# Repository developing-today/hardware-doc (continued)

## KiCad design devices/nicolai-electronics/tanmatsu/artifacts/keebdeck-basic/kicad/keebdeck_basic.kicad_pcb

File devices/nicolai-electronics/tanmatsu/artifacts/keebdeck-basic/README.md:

# KeebDeck Basic — reference-board schematic and KiCad source

Solder Party's **KeebDeck Basic** evaluation board — the reference design for driving a KeebDeck
keypad. The Tanmatsu does **not** ship this board; it is prior art for the Tanmatsu's own keyboard
section.

| | |
|---|---|
| `keebdeck-basic-schematic-rev1.1.pdf` | the exported schematic — filed 2026-09-20, mined in [`../../keyboard.md` §2b](../../keyboard.md) |
| `kicad/` | **the EDA source it was exported from** — added 2026-09-20, see §"KiCad source" |
| `mechanical/` | STEP models — **archived** 2026-09-20, placeholders in place |
| `LICENSE-CERN-OHL-v1.2.md` | upstream `LICENSE.md` — **read 2026-09-20**, see the correction below |
| `upstream-README.md` | upstream `README.md` |

## The PDF

`keebdeck-basic-schematic-rev1.1.pdf`

| Field | Value |
|---|---|
| What it is | Schematic of the **Solder Party KeebDeck Basic** evaluation board — the reference design for driving a KeebDeck keypad |
| Upstream repository | <https://github.com/solderparty/keebdeck_basic_hw> |
| Commit | **`2b537ce`** — commit subject *"Rev 1.1 - Production"* |
| Member path in repo | `schematics.pdf` |
| Source file | `keebdeck_basic.kicad_sch`, exported by KiCad E.D.A. **9.0.1** (Eeschema-PDF) |
| PDF `CreationDate` | **2025-05-04** |
| Title-block `Date:` / `Rev:` | **blank** — the "Rev 1.1" label comes from the Git commit only |
| Bytes | **355 080** |
| SHA-256 | `593aa32d45e70aaa331f82b558a5675666e5bd2d0f7f9584e36abfbb66b8b0a4` |
| Pages | 1 (A4 landscape, 841.896 × 595.296 pt) |
| Retrieved | **2026-08-24** (with the rest of the Tanmatsu source clones) |
| Filed here | **2026-09-20** |
| Renamed | from `schematics.pdf` → `keebdeck-basic-schematic-rev1.1.pdf` |
| Licence | **CERN Open Hardware Licence v1.2** — ✅ **resolved 2026-09-20**, see the correction below |
| Redistribution status | `conditional` — CERN-OHL v1.2 requires notice and licence retention |
| Disposition | `repository` |

> ### ✅ Correction — the licence is now known
>
> This record previously said: *"**unknown** — the upstream repo ships a `LICENSE.md` that was
> **not read** in this pass. The sibling `keebdeck_keyboard_hw` is CERN-OHL v1.2; do **not** assume
> the same applies here."* That caution was correct procedure and is now discharged.
>
> `LICENSE.md` (9 121 B) **was read on 2026-09-20** and is the **CERN Open Hardware Licence
> v1.2** — the same licence as `keebdeck_keyboard_hw` after all. It is retained here as
> `LICENSE-CERN-OHL-v1.2.md`.
>
> ⚠ The file contains **mojibake**: typographic quotes appear as `?` replacement characters
> (`?Licence? means this CERN OHL`). That is how upstream ships it — the bytes were **not**
> altered. It does not affect the licence's identity, which is stated in plain ASCII on line 1.

## Why this is a copy, not a move

`scratch/tanmatsu/sources/keebdeck_basic_hw/` is a **complete, unmodified `git` checkout** at
`2b537ce` (`git status` clean, 2026-09-20). Moving one file out of it would break a reproducible
upstream snapshot for no benefit, so the file was **copied** and the checkout left intact. The
same treatment was given to `keebdeck_keyboard_hw/dimensions.pdf` in the 2026-08-24 pass.

## What was mined out of it

See [`../../keyboard.md` §2b](../../keyboard.md#2b-verified-the-keebdeck-basic-reference-board-read-from-its-schematic).
The headline findings:

- The reference board is a **6 × 12 / 71-key** matrix, **not** the 6 × 13 the finished KeebDeck
  keypad and the Tanmatsu use.
- **No diodes in the matrix.** Ghosting is mitigated by swapping the TAB and E columns, per a
  note on the sheet.
- The **whole backlight block and the boot button are marked DNP**.
- **`ROW3` is `BOOT0`**, and **`COL0`/`COL1` are `SWDIO`/`SWCLK`** — three pins that are both
  matrix lines and system-critical.

## Re-acquisition

```bash
git clone https://github.com/solderparty/keebdeck_basic_hw
git -C keebdeck_basic_hw checkout 2b537ce
sha256sum keebdeck_basic_hw/schematics.pdf
# expect 593aa32d45e70aaa331f82b558a5675666e5bd2d0f7f9584e36abfbb66b8b0a4
```

Reacquisition status: **automatic**. Verified present at that commit on **2026-09-20** from the
local checkout; the GitHub URL was **not** re-probed in this pass.

---

## KiCad source · *added 2026-09-20*

The PDF above is an export. These are the files it was exported from — primary, load-bearing EDA
source, so they belong in the repository rather than the archive.

| File | Bytes | SHA-256 (first 16) |
|---|---:|---|
| `kicad/keebdeck_basic.kicad_sch` | 519 853 | `cc0ce3ffbe3693c6…` |
| `kicad/keebdeck_basic.kicad_pcb` | 2 928 754 | `39b66d2d24ff7a37…` |
| `kicad/keebdeck_basic.kicad_pro` | 16 331 | `4782c9f31bb75540…` |
| `kicad/keebdeck_basic_faceplate.kicad_pcb` | 379 374 | `141f51ef272c238b…` |
| `kicad/keebdeck_basic_faceplate.kicad_pro` | 14 179 | `14ce7942a8c5a528…` |
| `kicad/fp-lib-table`, `kicad/sym-lib-table` | 647 / 611 | library tables |

`keebdeck_basic.kicad_pcb` carries **resolved net names on every pad**, so it — not the PDF, and
not the `.kicad_sch` — is the authoritative statement of this board's connectivity. Re-parse with:

```bash
python3 tools/kicad_pcb_nets.py \
  devices/nicolai-electronics/tanmatsu/artifacts/keebdeck-basic/kicad/keebdeck_basic.kicad_pcb --all
```

### Not copied here

| Left in `scratch/tanmatsu/sources/keebdeck_basic_hw/` | Why |
|---|---|
| `fp-info-cache` (3 950 153 B) | KiCad footprint-index cache — regenerated on open |
| `library/`, `modules/`, `keebdeck_keyboard_hw/` | Git submodule/vendored library trees; the keypad library is already filed at [`../keebdeck-keyboard/`](../keebdeck-keyboard/README.md) |
| `img/basic.jpg` | Product photo, not needed for the electrical record |

## Mechanical models · **archived** 2026-09-20

| File | State | Bytes |
|---|---|---:|
| ~~`mechanical/keebdeck_basic.step`~~ | **archived** → `mechanical/keebdeck_basic.step.ARCHIVED.md` | 46 777 091 |
| ~~`mechanical/keebdeck_basic_faceplate.step`~~ | **archived** → `mechanical/keebdeck_basic_faceplate.step.ARCHIVED.md` | 2 846 452 |

Geometry only, for a board the Tanmatsu does not ship — the clearest possible archive case. Both
placeholders carry SHA-256, byte size, commit `2b537ce`, tag `rev1.1`, author, licence and two
independent recovery URLs, and stand alone without the archive.

## Why these are copies, not moves

Unchanged from the reasoning above: `scratch/tanmatsu/sources/keebdeck_basic_hw/` is a **clean,
unmodified checkout** at `2b537ce` (`git status` clean, 2026-09-20). Every file here was verified
**byte-identical by SHA-256** to its scratch counterpart at copy time; the STEP files were then
archived out of the repository by `tools/archive_artifact.py`, which re-verified content by
fingerprint after the move.

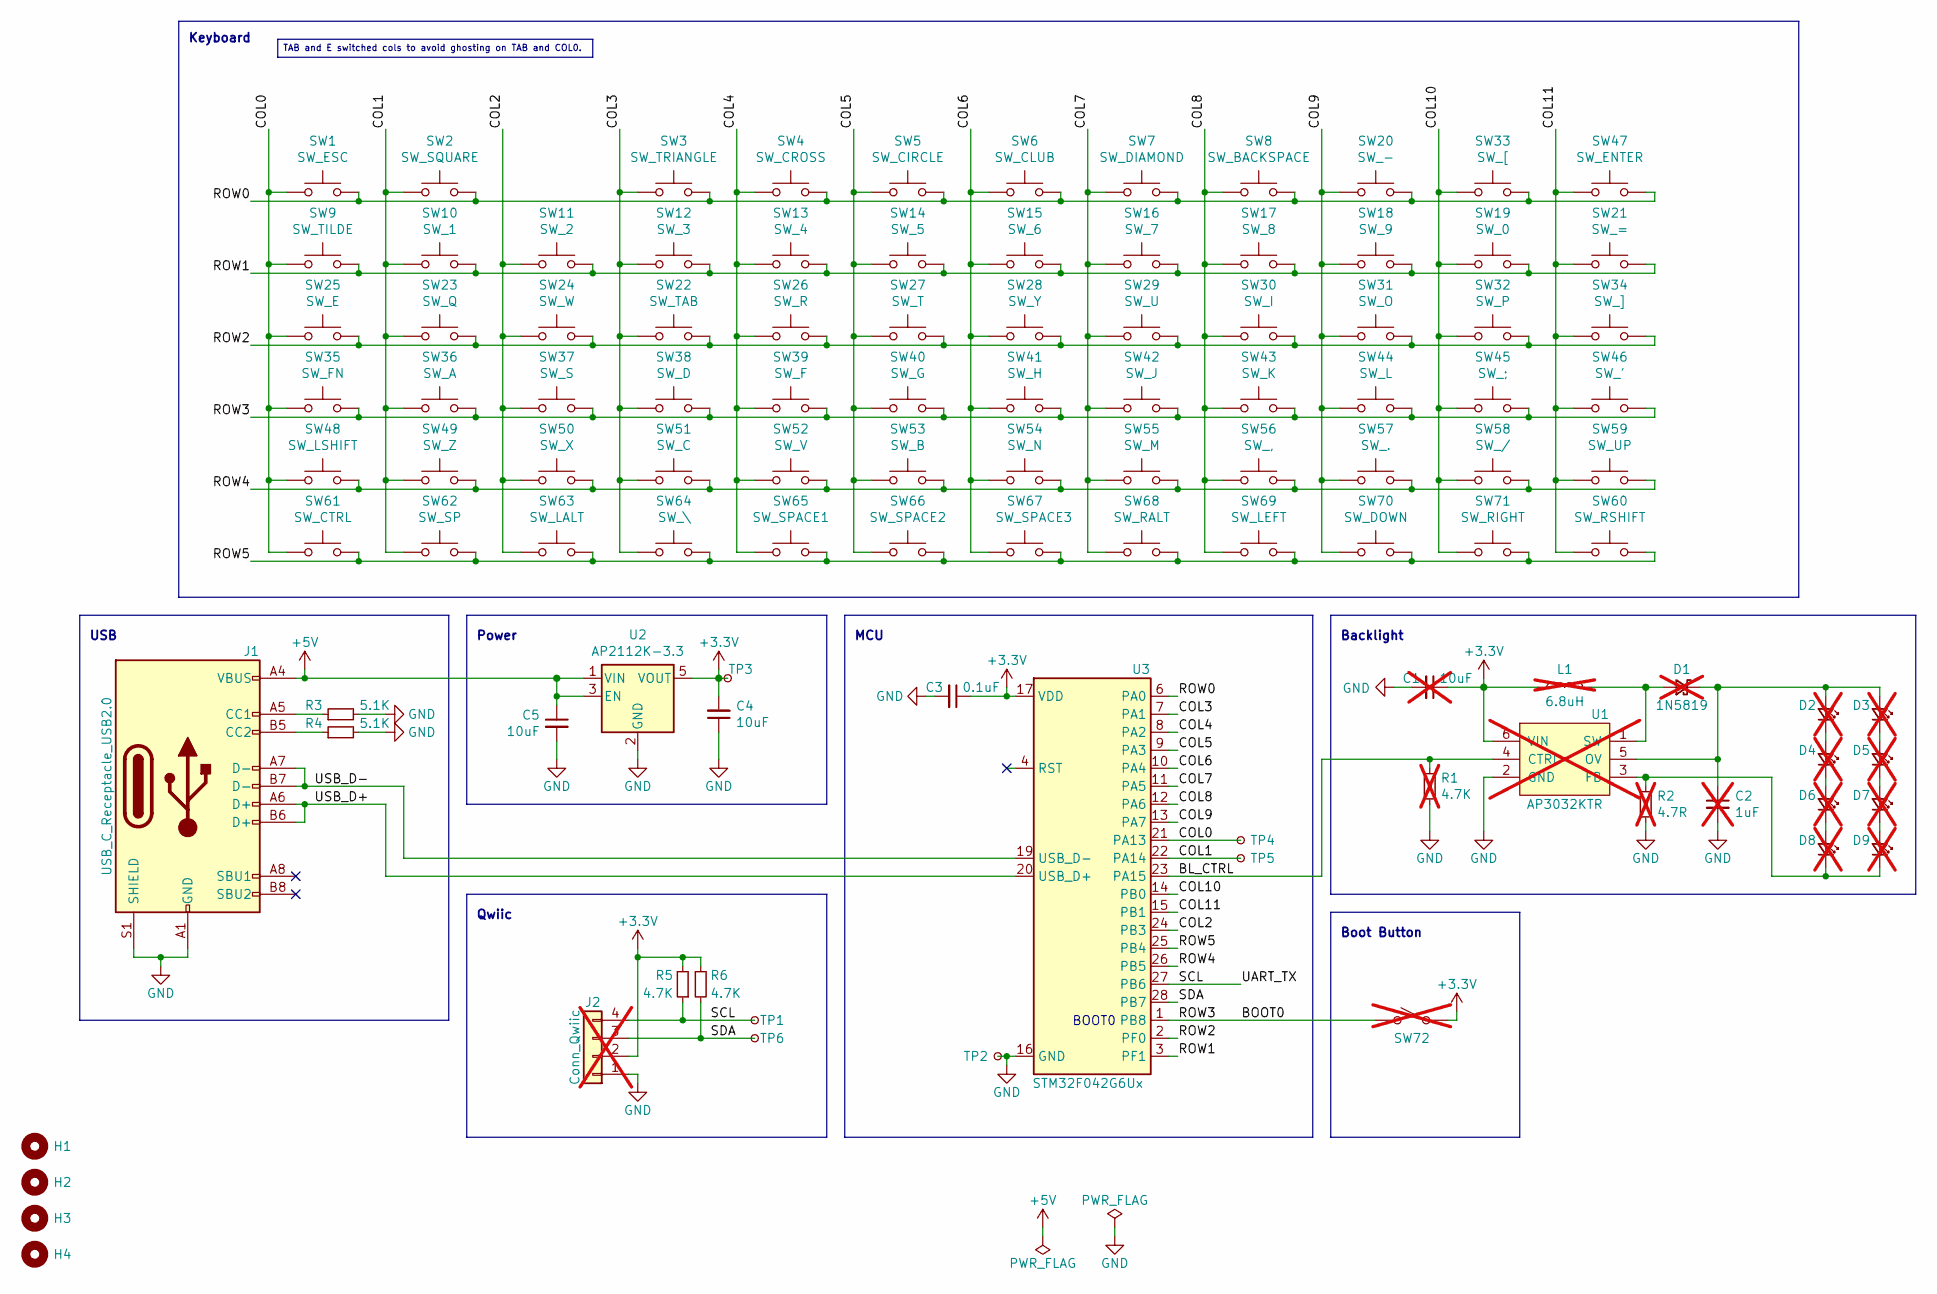
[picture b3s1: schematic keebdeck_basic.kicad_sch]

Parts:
C1: 10uF; C_0603_1608Metric; not fitted
C2: 1uF; C_0603_1608Metric; not fitted
C3: 0.1uF; C_0603_1608Metric
C4, C5: 10uF; C_0603_1608Metric
D1: 1N5819; D_SOD-323_HandSoldering; LCSC C369937; not fitted
D2, D3, D4, D5, D6, D7, D8, D9: LTW-010DCG-SR-G; LCSC C5175311; not fitted
H1, H2, H3, H4: MountingHole; SMD-1_BD4.4-D2.8; LCSC C5301775
J1: USB_C_Receptacle_USB2.0; USB_C_Receptacle_SHOU_HAN-TYPE-C-16P-CB1.6-073; LCSC C2906290
J2: Conn_Qwiic; JST_SH_SM04B-SRSS-TB_1x04-1MP_P1.00mm_Horizontal; LCSC C145956; not fitted
L1: 6.8uH; L_1008_2520Metric; LCSC C2041474; not fitted
R1: 4.7K; R_0603_1608Metric; not fitted
R2: 4.7R; R_0603_1608Metric; not fitted
R3, R4: 5.1K; R_0603_1608Metric
R5, R6: 4.7K; R_0603_1608Metric
SW1: SW_ESC; Metal_Dome_Oblong_5x4mm
SW2: SW_SQUARE; Metal_Dome_Oblong_5x4mm
SW3: SW_TRIANGLE; Metal_Dome_Oblong_5x4mm
SW4: SW_CROSS; Metal_Dome_Oblong_5x4mm
SW5: SW_CIRCLE; Metal_Dome_Oblong_5x4mm
SW6: SW_CLUB; Metal_Dome_Oblong_5x4mm
SW7: SW_DIAMOND; Metal_Dome_Oblong_5x4mm
SW8: SW_BACKSPACE; Metal_Dome_Oblong_5x4mm
SW9: SW_TILDE; Metal_Dome_Oblong_5x4mm
SW10: SW_1; Metal_Dome_Oblong_5x4mm
SW11: SW_2; Metal_Dome_Oblong_5x4mm
SW12: SW_3; Metal_Dome_Oblong_5x4mm
SW13: SW_4; Metal_Dome_Oblong_5x4mm
SW14: SW_5; Metal_Dome_Oblong_5x4mm
SW15: SW_6; Metal_Dome_Oblong_5x4mm
SW16: SW_7; Metal_Dome_Oblong_5x4mm
SW17: SW_8; Metal_Dome_Oblong_5x4mm
SW18: SW_9; Metal_Dome_Oblong_5x4mm
SW19: SW_0; Metal_Dome_Oblong_5x4mm
SW20: SW_-; Metal_Dome_Oblong_5x4mm
SW21: SW_=; Metal_Dome_Oblong_5x4mm
SW22: SW_TAB; Metal_Dome_Oblong_5x4mm
SW23: SW_Q; Metal_Dome_Oblong_5x4mm
SW24: SW_W; Metal_Dome_Oblong_5x4mm
SW25: SW_E; Metal_Dome_Oblong_5x4mm
SW26: SW_R; Metal_Dome_Oblong_5x4mm
SW27: SW_T; Metal_Dome_Oblong_5x4mm
SW28: SW_Y; Metal_Dome_Oblong_5x4mm
SW29: SW_U; Metal_Dome_Oblong_5x4mm
SW30: SW_I; Metal_Dome_Oblong_5x4mm
SW31: SW_O; Metal_Dome_Oblong_5x4mm
SW32: SW_P; Metal_Dome_Oblong_5x4mm
SW33: SW_[; Metal_Dome_Oblong_5x4mm
SW34: SW_]; Metal_Dome_Oblong_5x4mm
SW35: SW_FN; Metal_Dome_Oblong_5x4mm
SW36: SW_A; Metal_Dome_Oblong_5x4mm
SW37: SW_S; Metal_Dome_Oblong_5x4mm
SW38: SW_D; Metal_Dome_Oblong_5x4mm
SW39: SW_F; Metal_Dome_Oblong_5x4mm
SW40: SW_G; Metal_Dome_Oblong_5x4mm
SW41: SW_H; Metal_Dome_Oblong_5x4mm
SW42: SW_J; Metal_Dome_Oblong_5x4mm
SW43: SW_K; Metal_Dome_Oblong_5x4mm
SW44: SW_L; Metal_Dome_Oblong_5x4mm
SW45: SW_;; Metal_Dome_Oblong_5x4mm
SW46: SW_'; Metal_Dome_Oblong_5x4mm
SW47: SW_ENTER; Metal_Dome_Oblong_5x4mm
SW48: SW_LSHIFT; Metal_Dome_Oblong_5x4mm
SW49: SW_Z; Metal_Dome_Oblong_5x4mm
SW50: SW_X; Metal_Dome_Oblong_5x4mm
SW51: SW_C; Metal_Dome_Oblong_5x4mm
SW52: SW_V; Metal_Dome_Oblong_5x4mm
SW53: SW_B; Metal_Dome_Oblong_5x4mm
SW54: SW_N; Metal_Dome_Oblong_5x4mm
SW55: SW_M; Metal_Dome_Oblong_5x4mm
SW56: SW_,; Metal_Dome_Oblong_5x4mm
SW57: SW_.; Metal_Dome_Oblong_5x4mm
SW58: SW_/; Metal_Dome_Oblong_5x4mm
SW59: SW_UP; Metal_Dome_Oblong_5x4mm
SW60: SW_RSHIFT; Metal_Dome_Oblong_5x4mm
SW61: SW_CTRL; Metal_Dome_Oblong_5x4mm
SW62: SW_SP; Metal_Dome_Oblong_5x4mm
SW63: SW_LALT; Metal_Dome_Oblong_5x4mm
SW64: SW_\; Metal_Dome_Oblong_5x4mm
SW65: SW_SPACE1; Metal_Dome_Oblong_5x4mm
SW66: SW_SPACE2; Metal_Dome_Oblong_5x4mm
SW67: SW_SPACE3; Metal_Dome_Oblong_5x4mm
SW68: SW_RALT; Metal_Dome_Oblong_5x4mm
SW69: SW_LEFT; Metal_Dome_Oblong_5x4mm
SW70: SW_DOWN; Metal_Dome_Oblong_5x4mm
SW71: SW_RIGHT; Metal_Dome_Oblong_5x4mm
SW72: SW_BOOT; TS-1088R; LCSC C455280; not fitted
TP1: TP_SCL; TestPoint_Pad_D1.5mm
TP2, TP3: TP_UART_TX; TestPoint_Pad_D1.5mm
TP4: TP_SWDIO; TestPoint_Pad_D1.5mm
TP5: TP_SWCLK; TestPoint_Pad_D1.5mm
TP6: TP_SDA; TestPoint_Pad_D1.5mm
U1: AP3032KTR; SOT-23-6; LCSC C264086; not fitted
U2: AP2112K-3.3; SOT-23-5; LCSC C51118
U3: STM32F042G6Ux; QFN-28_4x4mm_P0.5mm; LCSC C961597

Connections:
+3.3V: C1.1, C3.1, C4.2, J2.2, L1.1, R5.2, R6.1, SW72.1 (A), TP3.1, U1.6 (VIN), U2.5 (VOUT), U3.5 (VDDA), U3.17 (VDD), U3.18 (VDDIO2)
+5V: C5.1, J1.A4 (VBUS), J1.A9 (VBUS), J1.B4 (VBUS), J1.B9 (VBUS), U2.1 (VIN), U2.3 (EN)
/BL_CTRL: R1.2, U1.4 (CTRL), U3.23 (PA15)
/BOOT0: SW35.2, SW36.2, SW37.2, SW38.2, SW39.2, SW40.2, SW41.2, SW42.2, SW43.2, SW44.2, SW45.2, SW46.2, SW72.2 (B), U3.1 (PB8)
/COL0: SW1.1, SW9.1, SW25.1, SW35.1, SW48.1, SW61.1, TP4.1, U3.21 (PA13)
/COL1: SW2.1, SW10.1, SW23.1, SW36.1, SW49.1, SW62.1, TP5.1, U3.22 (PA14)
/COL2: SW11.1, SW24.1, SW37.1, SW50.1, SW63.1, U3.24 (PB3)
/COL3: SW3.1, SW12.1, SW22.1, SW38.1, SW51.1, SW64.1, U3.7 (PA1)
/COL4: SW4.1, SW13.1, SW26.1, SW39.1, SW52.1, SW65.1, U3.8 (PA2)
/COL5: SW5.1, SW14.1, SW27.1, SW40.1, SW53.1, SW66.1, U3.9 (PA3)
/COL6: SW6.1, SW15.1, SW28.1, SW41.1, SW54.1, SW67.1, U3.10 (PA4)
/COL7: SW7.1, SW16.1, SW29.1, SW42.1, SW55.1, SW68.1, U3.11 (PA5)
/COL8: SW8.1, SW17.1, SW30.1, SW43.1, SW56.1, SW69.1, U3.12 (PA6)
/COL9: SW18.1, SW20.1, SW31.1, SW44.1, SW57.1, SW70.1, U3.13 (PA7)
/COL10: SW19.1, SW32.1, SW33.1, SW45.1, SW58.1, SW71.1, U3.14 (PB0)
/COL11: SW21.1, SW34.1, SW46.1, SW47.1, SW59.1, SW60.1, U3.15 (PB1)
/ROW0: SW1.2, SW2.2, SW3.2, SW4.2, SW5.2, SW6.2, SW7.2, SW8.2, SW20.2, SW33.2, SW47.2, U3.6 (PA0)
/ROW1: SW9.2, SW10.2, SW11.2, SW12.2, SW13.2, SW14.2, SW15.2, SW16.2, SW17.2, SW18.2, SW19.2, SW21.2, U3.3 (PF1)
/ROW2: SW22.2, SW23.2, SW24.2, SW25.2, SW26.2, SW27.2, SW28.2, SW29.2, SW30.2, SW31.2, SW32.2, SW34.2, U3.2 (PF0)
/ROW4: SW48.2, SW49.2, SW50.2, SW51.2, SW52.2, SW53.2, SW54.2, SW55.2, SW56.2, SW57.2, SW58.2, SW59.2, U3.26 (PB5)
/ROW5: SW60.2, SW61.2, SW62.2, SW63.2, SW64.2, SW65.2, SW66.2, SW67.2, SW68.2, SW69.2, SW70.2, SW71.2, U3.25 (PB4)
/SCL: J2.4, R5.1, TP1.1, U3.27 (PB6)
/SDA: J2.3, R6.2, TP6.1, U3.28 (PB7)
/USB_D+: J1.A6 (D+), J1.B6 (D+), U3.20 (USB_D+)
/USB_D-: J1.A7 (D-), J1.B7 (D-), U3.19 (USB_D-)
GND: C1.2, C2.2, C3.2, C4.1, C5.2, J1.A1 (GND), J1.A12 (GND), J1.B1 (GND), J1.B12 (GND), J1.S1 (SHIELD), J2.1, R1.1, R2.2, R3.2, R4.2, TP2.1, U1.2 (GND), U2.2 (GND), U3.16 (GND)
unnamed: D1.2 (A), L1.2, U1.1 (SW)
unnamed: C2.1, D1.1 (K), D2.2 (A), D3.2 (A), U1.5 (OV)
unnamed: D2.1 (K), D4.2 (A)
unnamed: D3.1 (K), D5.2 (A)
unnamed: D4.1 (K), D6.2 (A)
unnamed: D5.1 (K), D7.2 (A)
unnamed: D6.1 (K), D8.2 (A)
unnamed: D7.1 (K), D9.2 (A)
unnamed: D8.1 (K), D9.1 (K), R2.1, U1.3 (FB)
unnamed: J1.A5 (CC1), R3.1
unnamed: J1.B5 (CC2), R4.1

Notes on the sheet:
Keyboard
Boot Button
USB
Backlight
Qwiic
BOOT0
MCU
Power
TAB and E switched cols to avoid ghosting on TAB and COL0.

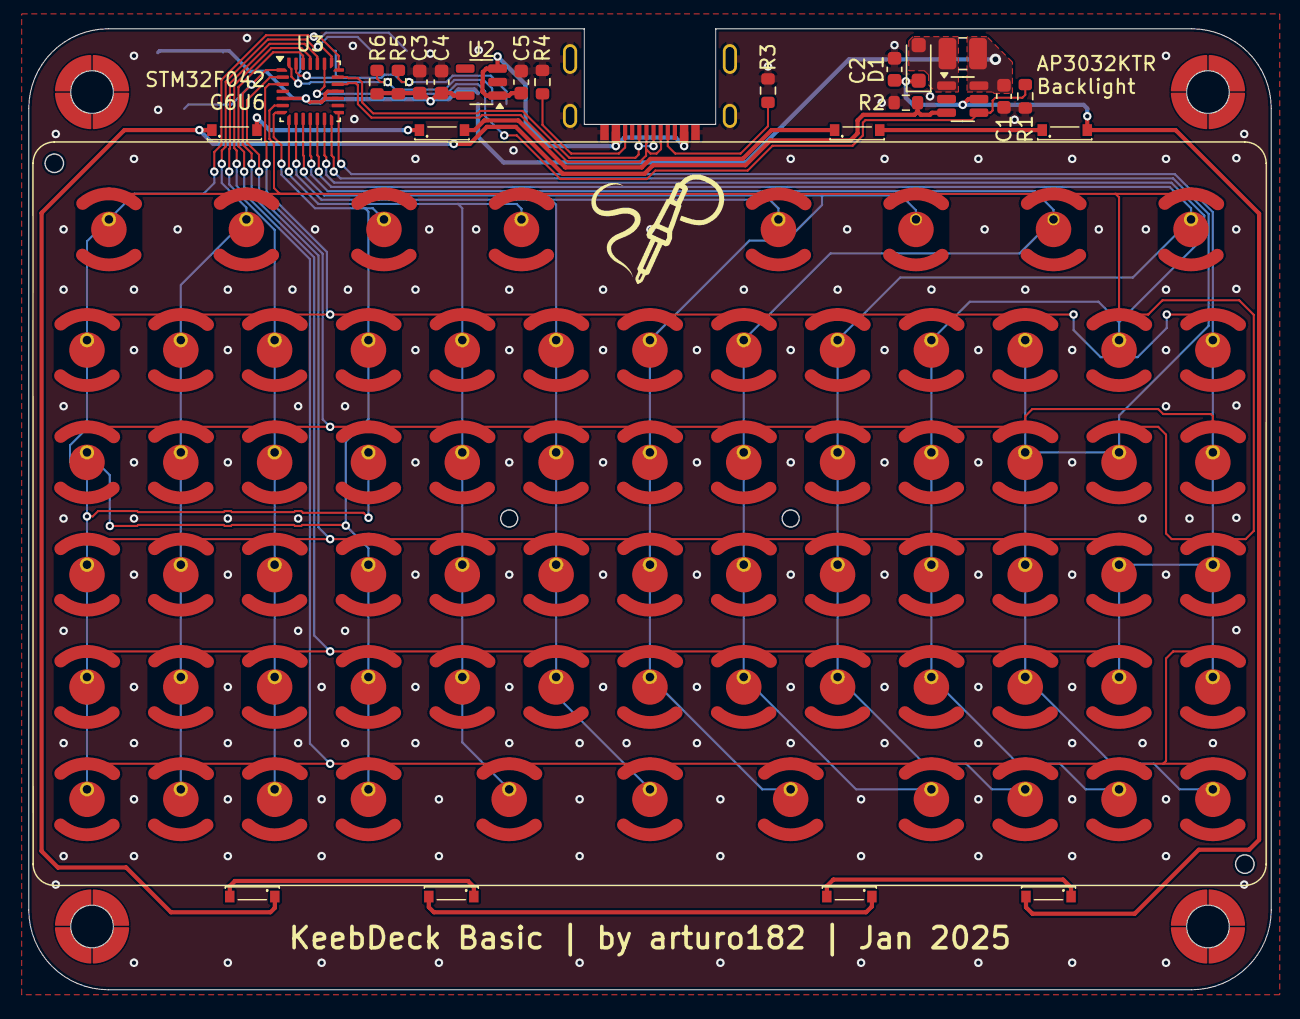
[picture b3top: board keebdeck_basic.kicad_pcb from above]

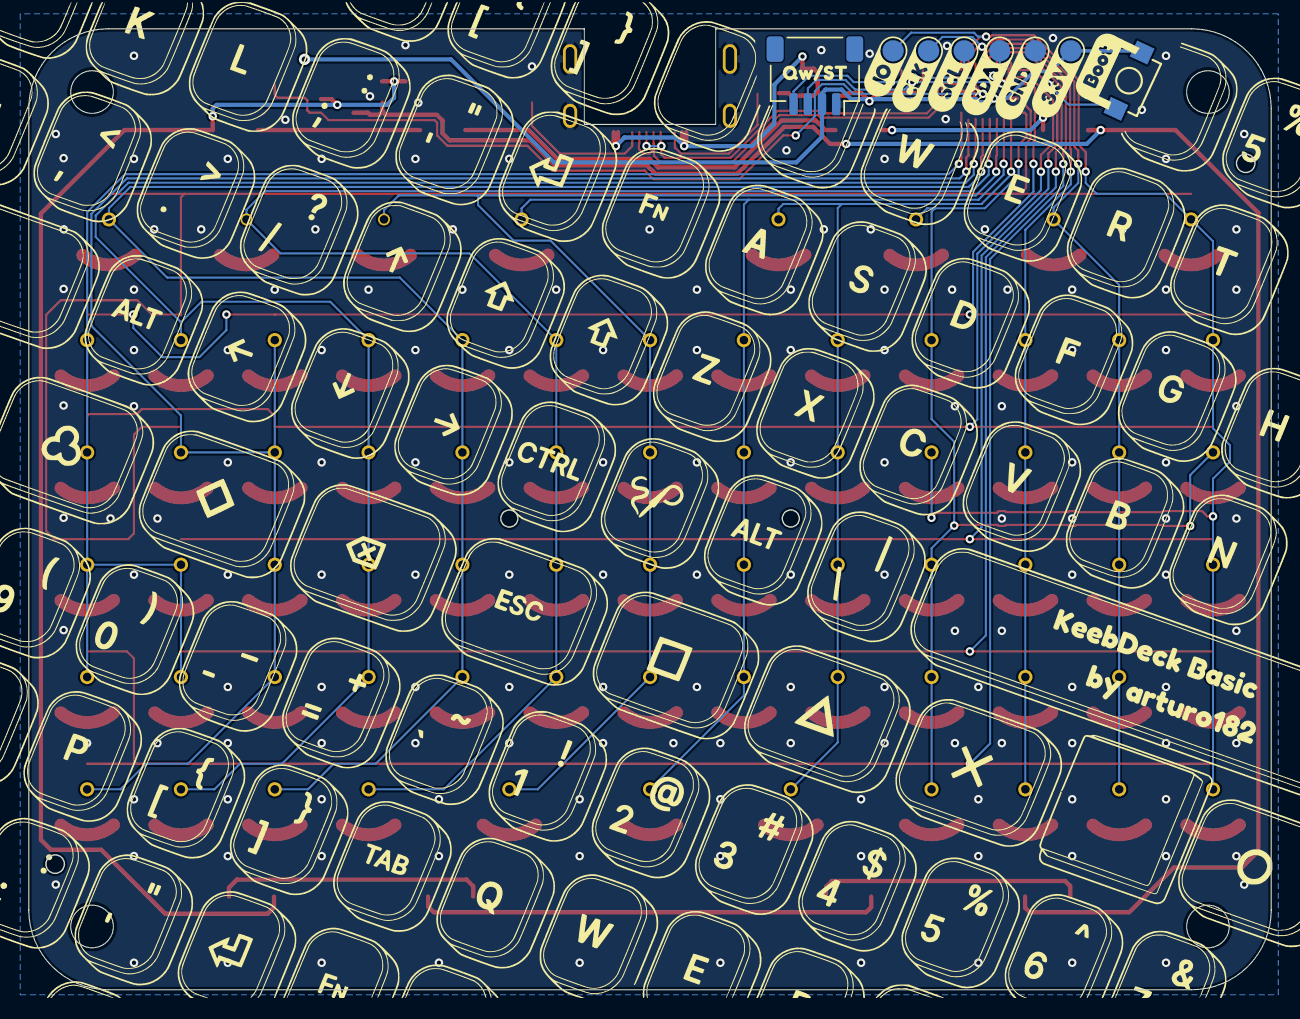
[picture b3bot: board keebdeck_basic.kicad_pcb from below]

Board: 2 copper layers, 87.4 x 67.6 mm, 118 parts (18 on the bottom side), 37 nets.

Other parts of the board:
kibuzzard-66E774B8: G***; kibuzzard-66E774B8
kibuzzard-67980A86: G***; kibuzzard-67980A86
kibuzzard-67980AB3: G***; kibuzzard-67980AB3
kibuzzard-67980AD7: G***; kibuzzard-67980AD7
kibuzzard-67980AE1: G***; kibuzzard-67980AE1
kibuzzard-67980AE6: G***; kibuzzard-67980AE6
kibuzzard-67980B11: G***; kibuzzard-67980B11
kibuzzard-67991D89: G***; kibuzzard-67991D89
kibuzzard-67991E3A: G***; kibuzzard-67991E3A
kibuzzard-6798348F: G***; kibuzzard-6798348F

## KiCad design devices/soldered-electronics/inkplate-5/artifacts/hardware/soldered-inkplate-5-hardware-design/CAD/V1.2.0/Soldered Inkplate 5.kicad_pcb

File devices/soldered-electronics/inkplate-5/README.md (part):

# Soldered Electronics — Inkplate 5 and Inkplate 5 Gen 2

> 5.2" Wi-Fi/BLE e-paper development boards with an ESP32-WROVER, from **Soldered Electronics** (Osijek, Croatia — formerly *e-radionica*).
> Research snapshot **2026-08-24**. Design data: **TAPR Open Hardware License** — redistribution permitted.

---

## The two generations differ in exactly one component

This is the headline result of comparing the two official KiCad BOMs, and it is not clearly stated on either product page.

| | **Inkplate 5** | **Inkplate 5 Gen 2** |
|---|---|---|
| Hardware design rev | **V1.2.0** | **V1.1.0** |
| E-paper panel | **`ED052TC2`** *(no component record — see [gaps §6](gaps-and-conflicts.md#6-no-e-ink-panel-datasheet))* | **[`ED052TC4`](../../../components/e-ink/ed052tc4/README.md)** |
| **Resolution** | **960 × 540** | **1280 × 720** |
| Diagonal | 5.2" | 5.2" |
| Processor | [ESP32-WROVER](../../../components/espressif/esp32-wrover/README.md) | [ESP32-WROVER](../../../components/espressif/esp32-wrover/README.md) |
| EPD PMIC | [TPS65186RGZ](../../../components/texas-instruments/tps65186/README.md) | [TPS65186RGZ](../../../components/texas-instruments/tps65186/README.md) |
| I/O expander | [PCAL6416AHF](../../../components/nxp/pcal6416a/README.md) | [PCAL6416AHF](../../../components/nxp/pcal6416a/README.md) |
| RTC | [PCF85063A](../../../components/nxp/pcf85063a/README.md) | [PCF85063A](../../../components/nxp/pcf85063a/README.md) |
| USB-UART | [CH340C](../../../components/wch/ch340c/README.md) | [CH340C](../../../components/wch/ch340c/README.md) |
| Charger | MCP73831T *(no component record)* | MCP73831T *(no component record)* |
| Arduino board define | `ARDUINO_INKPLATE5` | `ARDUINO_INKPLATE5V2` |
| Hardware repo | `Soldered-Inkplate-5-hardware-design` | `Soldered-Inkplate-5-Gen2-hardware-design` |

**Everything else is the same silicon.** Same module, same power architecture, same expander, same RTC, same bridge. Gen 2 is a panel upgrade — a 78 % pixel increase (518,400 → 921,600 px) at the same physical size, so ~1.78× the pixel density.

Resolutions confirmed from the Arduino library's own headers:

```c
// src/boards/Inkplate5/waveforms.h        (ARDUINO_INKPLATE5)
#define E_INK_WIDTH  960
#define E_INK_HEIGHT 540

// src/boards/Inkplate5V2/waveforms.h      (ARDUINO_INKPLATE5V2)
#define E_INK_WIDTH  1280
#define E_INK_HEIGHT 720
```

Note the library calls it **`Inkplate5V2`** while the store and repository call it **"Gen 2"**. Both refer to the same board. When selecting the target in Arduino you want **`Inkplate5V2`**.

> **Which one does ZeroWriter Ink use?** The **Gen 2 / V2** panel (`ED052TC4`, 1280×720) — on a [respun board](../../zerowriter/zerowriter-ink/README.md#the-second-important-fact-this-is-not-a-stock-inkplate-5), not the stock product.

## Complete bill of materials (Inkplate 5, V1.2.0)

Parsed from Soldered's own `OUTPUTS/V1.2.0/Soldered Inkplate 5 BOM.csv`.

| Ref | Part | Function |
|---|---|---|
| **U10** *(U11 on Gen 2)* | **[ESP32-WROVER](../../../components/espressif/esp32-wrover/README.md)** | Dual-core ESP32 module with PSRAM. PSRAM is essential — a 1280×720 framebuffer does not fit in internal RAM |
| **U11** *(U9 on Gen 2)* | **`ED052TC2`** / **[`ED052TC4`](../../../components/e-ink/ed052tc4/README.md)** | E Ink panel. Only the Gen 2's `ED052TC4` has a component record; **no record exists for the `ED052TC2`**, and no manufacturer datasheet exists for either — [gaps §6](gaps-and-conflicts.md#6-no-e-ink-panel-datasheet) |
| **U1** | **[TPS65186RGZ](../../../components/texas-instruments/tps65186/README.md)** (VQFN-49) | E-paper PMIC — generates the ±15 V / ±22 V and VCOM rails |
| **U9** *(U10 on Gen 2)* | **[PCAL6416AHF](../../../components/nxp/pcal6416a/README.md)** | 16-bit I²C GPIO expander @ **0x20** — carries the EPD control lines and SD power |
| **U7** | **[PCF85063A](../../../components/nxp/pcf85063a/README.md)** | RTC (with `X1` = 32.768 kHz ABS07AIG) |
| **U3** | **[CH340C](../../../components/wch/ch340c/README.md)** (SOP-16) | [USB-UART bridge](../../../components/wch/ch340x/README.md) |
| **U4** | **MCP73831T** *(no component record)* | Linear LiPo charger — see [charger and power path](../../../components/generic/charger-power-path/README.md) for the generic interface |
| **U6** | **TPS7A2633DRVR** *(no component record)* | 3.3 V LDO |
| **U2** | **TPS3840PL27DBVR** *(no component record)* | Voltage supervisor |
| **U8** | **SN74LVC1G34DBV** *(no component record)* | Single buffer |
| **U5** | **MC14093BDTR2G** *(no component record)* | Quad Schmitt NAND |
| **R2** | **NCP18XH103F03RB** NTC *(no component record)* | Panel temperature sense — e-paper waveforms are temperature-dependent |
| L1 / L2 | LQH44PN4R7MP0L / NR4012T2R2M | TPS65186 boost inductors |
| F1 | 1206, 500 mA | Fuse |
| **K11** | HYC77-TF09-200 | [microSD socket](../../../components/generic/micro-sd-sdmmc/README.md) |
| **K10** | **CR2032-BS-6-1** | **RTC backup coin-cell holder — footprint present, [ships unpopulated](features/rtc-backup-battery.md)** |
| SW1/SW2/SW3 | — | Reset / wake / user buttons |
| D9, D8 | — | Status LEDs |
| Q1 | **DNP** | Unpopulated |

⚠ **Designators shift between generations:** on the Inkplate 5 `K10` is the coin cell and `K11` the microSD; on the **Gen 2** `K11` is the coin cell. Read the silkscreen, not the other generation's table.

Plus **34 × `HEADER_MALE_1X1_Inkplate`** — the broken-out GPIO/peripheral header pads along the board edge.

Parts marked *(no component record)* are named in the BOM but have no entry under
[`components/`](../../../components/README.md). They are power, supervisory and glue logic that no
claim in this record depends on; creating records for them is an open follow-up.

## How the e-paper interface actually works

This is the interesting engineering in the Inkplate family and it is worth understanding before writing any code.

A parallel ("DES"-style) E Ink panel needs an 8-bit data bus clocked out at high rate, plus several timing signals. The ESP32 has no LCD peripheral. Soldered's solution: **drive the panel with the ESP32's I2S1 peripheral in parallel output mode, fed by DMA.**

From `Inkplate5V2Driver.cpp`:

```c
setI2S1pin(4,  I2S1O_DATA_OUT0_IDX, 0);   // D0
setI2S1pin(5,  I2S1O_DATA_OUT1_IDX, 0);   // D1
setI2S1pin(18, I2S1O_DATA_OUT2_IDX, 0);   // D2
setI2S1pin(19, I2S1O_DATA_OUT3_IDX, 0);   // D3
setI2S1pin(23, I2S1O_DATA_OUT4_IDX, 0);   // D4
setI2S1pin(25, I2S1O_DATA_OUT5_IDX, 0);   // D5
setI2S1pin(26, I2S1O_DATA_OUT6_IDX, 0);   // D6
setI2S1pin(27, I2S1O_DATA_OUT7_IDX, 0);   // D7
```

### Signal map

| Signal | Where it lives | Detail |
|---|---|---|
| `D0`–`D7` | **GPIO 4, 5, 18, 19, 23, 25, 26, 27** | I2S1 parallel data out, DMA-fed |
| `CL` (line clock) | **GPIO 0** | Bit-banged via `GPIO.out_w1ts/w1tc` = `0x01` |
| `LE` (latch enable) | **GPIO 2** | `GPIO.out` bit `0x04` |
| `CKV` | **GPIO 32** | `GPIO.out1` bit `0x01` |
| `SPH` | **GPIO 33** | `GPIO.out1` bit `0x02` |
| `OE` (output enable) | **expander pin 0** | via [PCAL6416A](../../../components/nxp/pcal6416a/README.md) |
| `GMOD` | **expander pin 1** | via [PCAL6416A](../../../components/nxp/pcal6416a/README.md) |
| `SPV` | **expander pin 2** | via [PCAL6416A](../../../components/nxp/pcal6416a/README.md) |
| `WAKEUP` | **expander pin 3** | [TPS65186](../../../components/texas-instruments/tps65186/README.md) wake |
| `PWRUP` | **expander pin 4** | [TPS65186](../../../components/texas-instruments/tps65186/README.md) power-up |
| `VCOM` | **expander pin 5** | [TPS65186](../../../components/texas-instruments/tps65186/README.md) VCOM control |
| [SD card](../../../components/generic/micro-sd-sdmmc/README.md) power MOSFET | **expander pin B2 (10)** | `SD_PMOS_PIN` — SD can be fully depowered for sleep |

Three consequences that matter:

1. **GPIO 0, 2, 4, 5, 18, 19, 23, 25, 26, 27, 32, 33 are all committed to the display.** That is most of the usable ESP32 GPIO. The broken-out header exposes what is left, and you should assume very little is free while the display is in use. GPIO 0 and 2 are also ESP32 **strapping pins** — they are shared with the boot mode selection.
2. **The slow control signals are behind I²C.** Every `OE`/`GMOD`/`SPV` toggle is an I²C transaction on the [PCAL6416A](../../../components/nxp/pcal6416a/README.md) at 0x20. This is why refresh sequencing is structured the way it is, and why you should not expect to bit-bang your own waveforms at speed.
3. **The SD card is switchable.** `SD_PMOS_PIN` on the expander gates [SD](../../../components/generic/micro-sd-sdmmc/README.md) power, which is how the Inkplate reaches low deep-sleep figures. If you drive the SD directly without powering it up first, it simply will not respond.

## Software

| Project | Repo | Licence | Notes |
|---|---|---|---|
| **Inkplate Arduino library** | `SolderedElectronics/Inkplate-Arduino-library` (306★) | **LGPL-3.0** | The main path. Covers Inkplate 2, 5, 5V2, 6, 6PLUS, 6COLOR, 6FLICK, 10, 4TEMPERA, 13SPECTRA |
| MicroPython driver | `SolderedElectronics/Inkplate-micropython` (91★) | MIT | |
| ESP-IDF component | `SolderedElectronics/Inkplate-ESP-IDF-component` | GPL-3.0 | |
| ESPHome component | `SolderedElectronics/Soldered-Inkplate-ESPHome` | GPL-3.0 | External component, SPI Inkplates |
| LVGL library | `SolderedElectronics/Inkplate-LVGL-Library` | GPL-3.0 | |
| Documentation | `SolderedElectronics/Inkplate-documentation` | — | readthedocs source |
| GUI Designer | `SolderedElectronics/Inkplate-GUI-Designer` | — | Web UI designer |
| Image converter | `SolderedElectronics/Inkplate-image-converter` | — | Web tool |

Notable third-party work: **[`turgu1/EPub-InkPlate`](https://github.com/turgu1/EPub-InkPlate)** (307★) — a full EPub reader, the highest-starred Inkplate application and the strongest evidence that the platform is viable for text-heavy devices. Also `turgu1/ESP-IDF-InkPlate` (ESP-IDF port) and `martinberlin/inkplate-platformio`.

## The Inkplate family

| Model | Panel | Notes |
|---|---|---|
| Inkplate 2 | 2.13", colour | SPI panel, small |
| **Inkplate 5** | 5.2" **960×540** | ESP32-WROVER |
| **Inkplate 5 Gen 2 / V2** | 5.2" **1280×720** | ESP32-WROVER; used by ZeroWriter Ink |
| Inkplate 6 | 5.83"/6" | The original, 1,312 % funded on Crowd Supply, 969 backers |
| Inkplate 6PLUS | 6" + touch + frontlight | |
| Inkplate 6COLOR | 6" colour | SPI panel |
| Inkplate 6FLICK | 6" | |
| Inkplate 10 | 9.7" | The large one |
| Inkplate 4 TEMPERA | 4" + glass panel, sensors | |
| Inkplate 13 SPECTRA | 13", Spectra colour | |
| **Inkplate 6 MOTION** | 6" | Separate Arduino library (`Inkplate_Motion_Arduino_Library`) — a different architecture |

Board list taken from `src/boards/` in the Arduino library — the authoritative list of what is actually supported.

## Family comparison

Soldered's own figures for the current (Soldered-era) boards, from `features.rst`:

| | Inkplate 2 | **Inkplate 5** | **Inkplate 5 V2** | Inkplate 6 | 6COLOR | 6PLUS | 6FLICK | Inkplate 10 | 4TEMPERA |
|---|---|---|---|---|---|---|---|---|---|
| Screen | 2.13" | **5.2"** | **5.2"** | 6" | 5.8" | 6" | 6" | 9.7" | 3.8" |
| Resolution | 202×104 | **960×540** | **1280×720** | 800×600 | 600×448 | 1024×758 | 1024×758 | 1200×825 | 600×600 |
| Pixels | 21,008 | **518,400** | **921,600** | 480,000 | 268,800 | 776,192 | 776,192 | 990,000 | 360,000 |
| Greyscale | – | **8** | **8** | 8 | – | 8 | 8 | 8 | 8 |
| Colour | Yes | No | No | No | **Yes** | No | No | No | No |
| Touchscreen | No | **No** | **No** | No | No | Yes | Yes | No | Yes |
| Backlight | No | **No** | **No** | No | No | Yes | Yes | No | Yes |
| microSD | No | **Yes** | **Yes** | Yes | Yes | Yes | Yes | Yes | Yes |
| **Full refresh** | 21 s | **1.02 s** | **1.13 s** | 1.26 s | 12 s | 1.27 s | 1.55 s | 1.61 s | 0.86 s |
| **Fast refresh** | – | **0.12 s** | **0.26 s** | 0.26 s | – | 0.64 s | 0.23 s | 0.62 s | 0.18 s |

Two things stand out. **The Inkplate 5 has the fastest refresh in the family** — 1.02 s full and 0.12 s fast, quicker than the physically smaller Inkplate 6. And the **Gen 2 costs surprisingly little for 78 % more pixels**: full refresh rises only 11 % (1.02 → 1.13 s), because full-refresh time is dominated by the e-paper waveform duration rather than data transfer. Fast refresh roughly doubles (0.12 → 0.26 s), where transfer time is a larger fraction of the total.

For a device like [ZeroWriter Ink](../../zerowriter/zerowriter-ink/README.md) that needs to keep up with typing, the **0.26 s fast refresh** is the number that matters — and it explains the campaign's "variable refresh rate produces almost no perceptible lag" claim being at least architecturally plausible.

Colour boards (Inkplate 2, 6COLOR) pay enormously for colour: 12–21 s full refresh and no fast-refresh mode at all.

## Component records

Every fitted part with a reusable record under [`components/`](../../../components/README.md).
Each links back here from its **Used By** section.

| Part | Role on this board | Record |
|---|---|---|
| ESP32-WROVER | Main processor module (PSRAM essential for the framebuffer) | [`espressif/esp32-wrover`](../../../components/espressif/esp32-wrover/README.md) |
| ED052TC4 | E Ink panel — **Gen 2 only**; the Inkplate 5's `ED052TC2` has no record | [`e-ink/ed052tc4`](../../../components/e-ink/ed052tc4/README.md) |
| TPS65186RGZ | E-paper PMIC, ±15 V / ±22 V and VCOM rails | [`texas-instruments/tps65186`](../../../components/texas-instruments/tps65186/README.md) |
| PCAL6416AHF | I²C GPIO expander @ 0x20 — EPD control lines and SD power gate | [`nxp/pcal6416a`](../../../components/nxp/pcal6416a/README.md) |
| PCF85063A | Real-time clock | [`nxp/pcf85063a`](../../../components/nxp/pcf85063a/README.md) |
| CH340C | USB-UART bridge | [`wch/ch340c`](../../../components/wch/ch340c/README.md) · generic: [`usb-uart-bridge`](../../../components/wch/ch340x/README.md) |
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
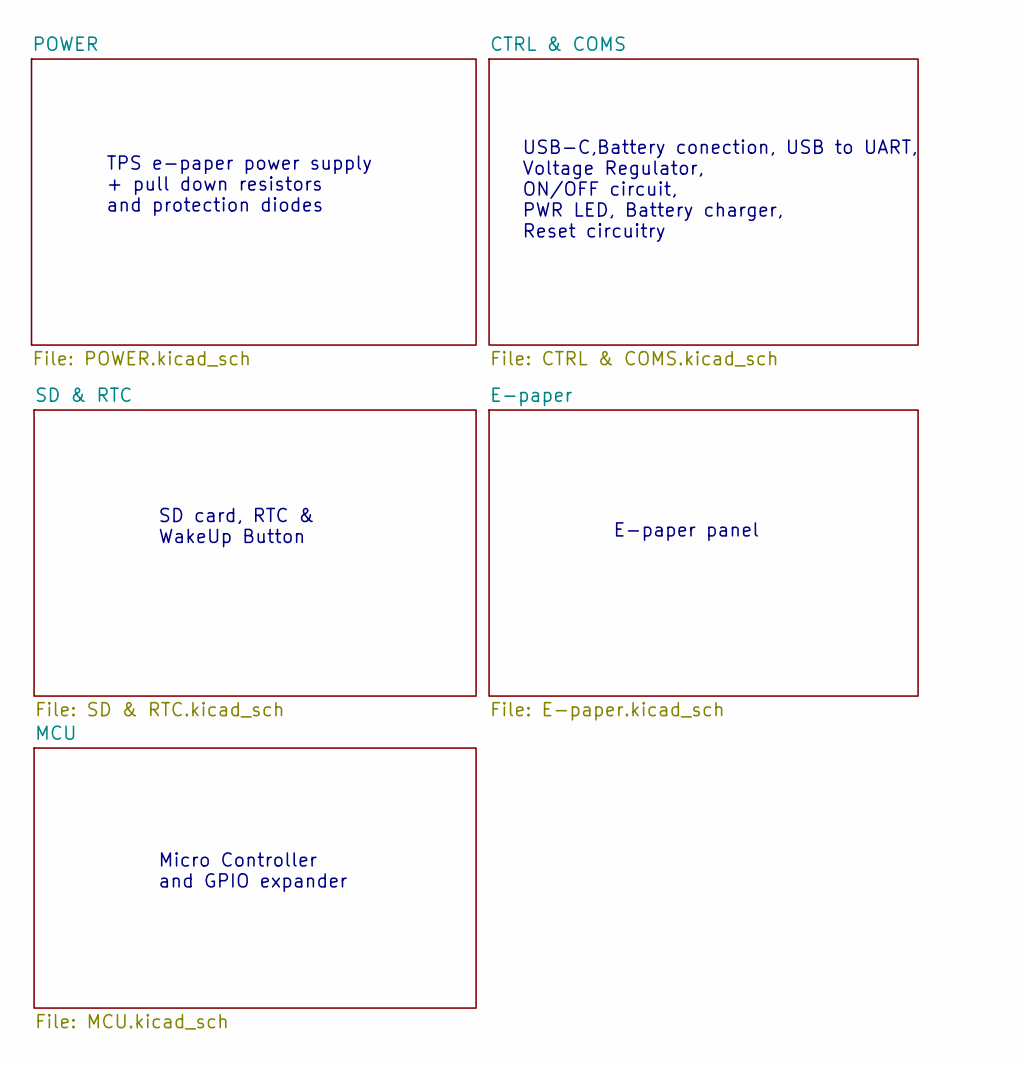
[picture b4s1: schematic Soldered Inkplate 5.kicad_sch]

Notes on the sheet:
USB-C,Battery conection, USB to UART, Voltage Regulator, ON/OFF circuit, PWR LED, Battery charger, Reset circuitry
SD card, RTC & WakeUp Button
Micro Controller and GPIO expander
TPS e-paper power supply + pull down resistors and protection diodes
E-paper panel

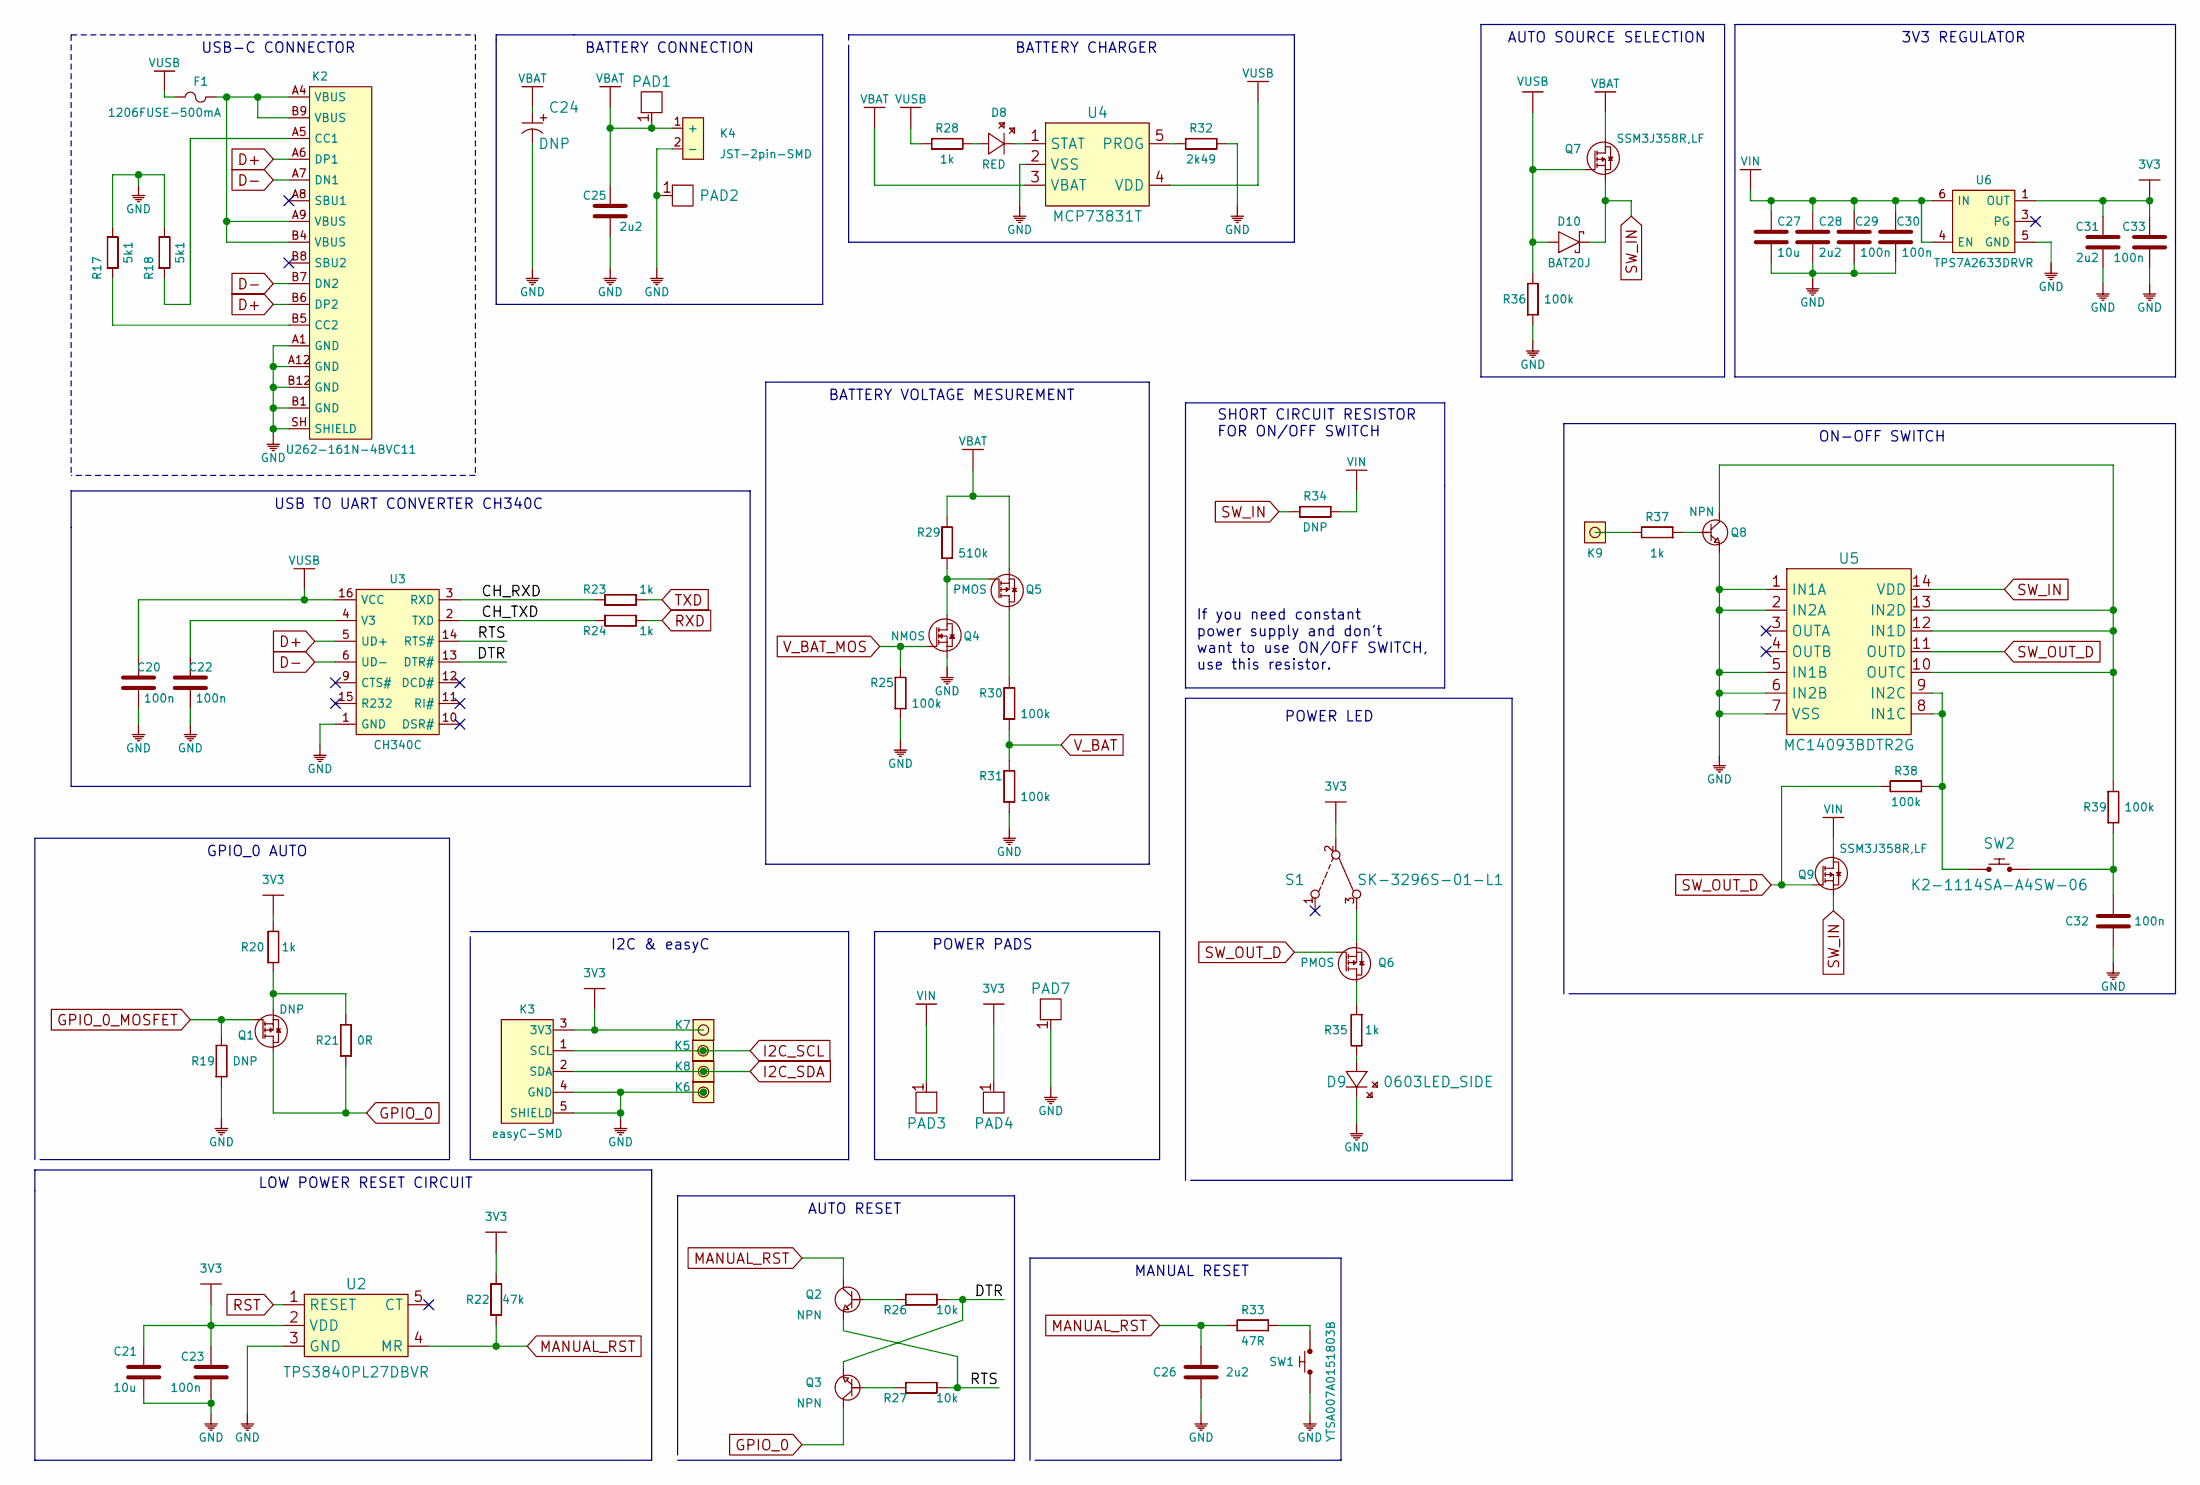
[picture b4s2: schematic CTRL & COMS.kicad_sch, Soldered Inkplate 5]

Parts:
C20, C22, C23, C29, C30, C32, C33: 100n; 0603C
C21, C27: 10u; 1206C
C24: DNP; 2917C
C25, C26, C28, C31: 2u2; 0603C
D8: RED; 0402LED
D9: 0603LED_SIDE; LTST-S270GKT
D10: BAT20J; SOD-323
F1: 1206FUSE-500mA; 1206FUSE
K2: U262-161N-4BVC11
K3: easyC-SMD; easyC-connector
K4: JST-2pin-SMD
K5, K6, K7, K8, K9: HEADER_MALE_1X1_Inkplate
PAD1, PAD2, PAD3, PAD4, PAD7: PAD_4x4
Q1: DNP; SOT-23-3
Q2, Q3, Q8: NPN; SOT-23-3
Q4: NMOS; SOT-23-3
Q5, Q6: PMOS; SOT-23-3
Q7, Q9: SSM3J358R,LF; SOT-23-3
R17, R18: 5k1; 0603R
R19, R34: DNP; 0603R
R20, R23, R24, R28, R35, R37: 1k; 0603R
R21: 0R; 0603R
R22: 47k; 0603R
R25, R30, R31, R36, R38, R39: 100k; 0603R
R26, R27: 10k; 0603R
R29: 510k; 0603R
R32: 2k49; 0603R
R33: 47R; 0603R
S1: SK-3296S-01-L1
SW1: YTSA007A0151803B
SW2: K2-1114SA-A4SW-06
U2: TPS3840PL27DBVR; SOT-23-5
U3: CH340C; SOP-16
U4: MCP73831T; SOT-23-5
U5: MC14093BDTR2G; TSSOP-14
U6: TPS7A2633DRVR

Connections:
3V3: C21.2, C23.2, C31.2, C33.2, K3.3 (3V3), K7.1, PAD4.1, R20.2, R22.2, S1.2, U2.2 (VDD), U6.1 (OUT); also elsewhere on the board
/CTRL & COMS/CH_RXD: R23.1, U3.3 (RXD)
/CTRL & COMS/CH_TXD: R24.1, U3.2 (TXD)
/CTRL & COMS/DTR: Q3.2 (E), R26.2, U3.13 (DTR#)
/CTRL & COMS/RTS: Q2.2 (E), R27.2, U3.14 (RTS#)
D+: K2.A6 (DP1), K2.B6 (DP2), U3.5 (UD+)
D-: K2.A7 (DN1), K2.B7 (DN2), U3.6 (UD-)
GND: C20.1, C21.1, C22.1, C23.1, C24.2 (-), C25.1, C26.1, C27.1, C28.1, C29.1, C30.1, C31.1, C32.1, C33.1, D9.2 (K), K2.A1 (GND), K2.A12 (GND), K2.B1 (GND), K2.B12 (GND), K2.SH (SHIELD), K3.4 (GND), K3.5 (SHIELD), K4.2 (-), K6.1, PAD2.1, PAD7.1, Q4.2 (S), Q8.2 (E), R17.2, R18.2, R19.1, R25.1, R31.1, R32.2, R36.1, SW1.1, U2.3 (GND), U3.1 (GND), U4.2 (VSS), U5.1 (IN1A), U5.2 (IN2A), U5.5 (IN1B), U5.6 (IN2B), U5.7 (VSS), U6.5 (GND); also elsewhere on the board
GPIO_0: Q1.3 (D), Q3.3 (C), R21.1; also elsewhere on the board
GPIO_0_MOSFET: Q1.1 (G), R19.2; also elsewhere on the board
I2C_SCL: K3.1 (SCL), K5.1; also elsewhere on the board
I2C_SDA: K3.2 (SDA), K8.1; also elsewhere on the board
MANUAL_RST: C26.2, Q2.3 (C), R22.1, R33.2, U2.4 (MR)
unnamed: C22.2, U3.4 (V3)
unnamed: C32.2, R39.1, SW2.2
unnamed: D8.1 (A), R28.2
unnamed: D8.2 (K), U4.1 (STAT)
unnamed: D9.1 (A), R35.2
unnamed: F1.2, K2.A4 (VBUS), K2.A9 (VBUS), K2.B4 (VBUS), K2.B9 (VBUS)
unnamed: K2.A5 (CC1), R18.1
unnamed: K2.B5 (CC2), R17.1
unnamed: K9.1, R37.2
unnamed: Q1.2 (S), R20.1, R21.2
unnamed: Q2.1 (B), R26.1
unnamed: Q3.1 (B), R27.1
unnamed: Q4.3 (D), Q5.1 (G), R29.1
unnamed: Q5.3 (D), R30.2
unnamed: Q6.2 (S), S1.3
unnamed: Q6.3 (D), R35.1
unnamed: Q8.1 (B), R37.1
unnamed: Q8.3 (C), R39.2, U5.10 (OUTC), U5.12 (IN1D), U5.13 (IN2D)
unnamed: R32.1, U4.5 (PROG)
unnamed: R33.1, SW1.2
unnamed: R38.1, SW2.1, U5.8 (IN1C), U5.9 (IN2C)
RST: U2.1 (RESET); also elsewhere on the board
RXD: R24.2; also elsewhere on the board
SW_IN: D10.2 (C), Q7.2 (S), Q9.2 (S), R34.1, U5.14 (VDD)
SW_OUT_D: Q6.1 (G), Q9.1 (G), R38.2, U5.11 (OUTD)
TXD: R23.2; also elsewhere on the board
VBAT: C24.1 (+), C25.2, K4.1 (+), PAD1.1, Q5.2 (S), Q7.3 (D), R29.2, U4.3 (VBAT); also elsewhere on the board
VIN: C27.2, C28.2, C29.2, C30.2, PAD3.1, Q9.3 (D), R34.2, U6.4 (EN), U6.6 (IN); also elsewhere on the board
VUSB: C20.2, D10.1 (A), F1.1, Q7.1 (G), R28.1, R36.2, U3.16 (VCC), U4.4 (VDD)
V_BAT: R30.1, R31.2; also elsewhere on the board
V_BAT_MOS: Q4.1 (G), R25.2; also elsewhere on the board

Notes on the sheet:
LOW POWER RESET CIRCUIT
AUTO RESET
GPIO_0 AUTO
ON-OFF SWITCH
BATTERY VOLTAGE MESUREMENT
AUTO SOURCE SELECTION
MANUAL RESET
USB-C CONNECTOR
I2C & easyC
BATTERY CHARGER
USB TO UART CONVERTER CH340C
POWER LED
BATTERY CONNECTION
SHORT CIRCUIT RESISTOR FOR ON/OFF SWITCH
3V3 REGULATOR
If you need constant power supply and don't want to use ON/OFF SWITCH, use this resistor.
POWER PADS
